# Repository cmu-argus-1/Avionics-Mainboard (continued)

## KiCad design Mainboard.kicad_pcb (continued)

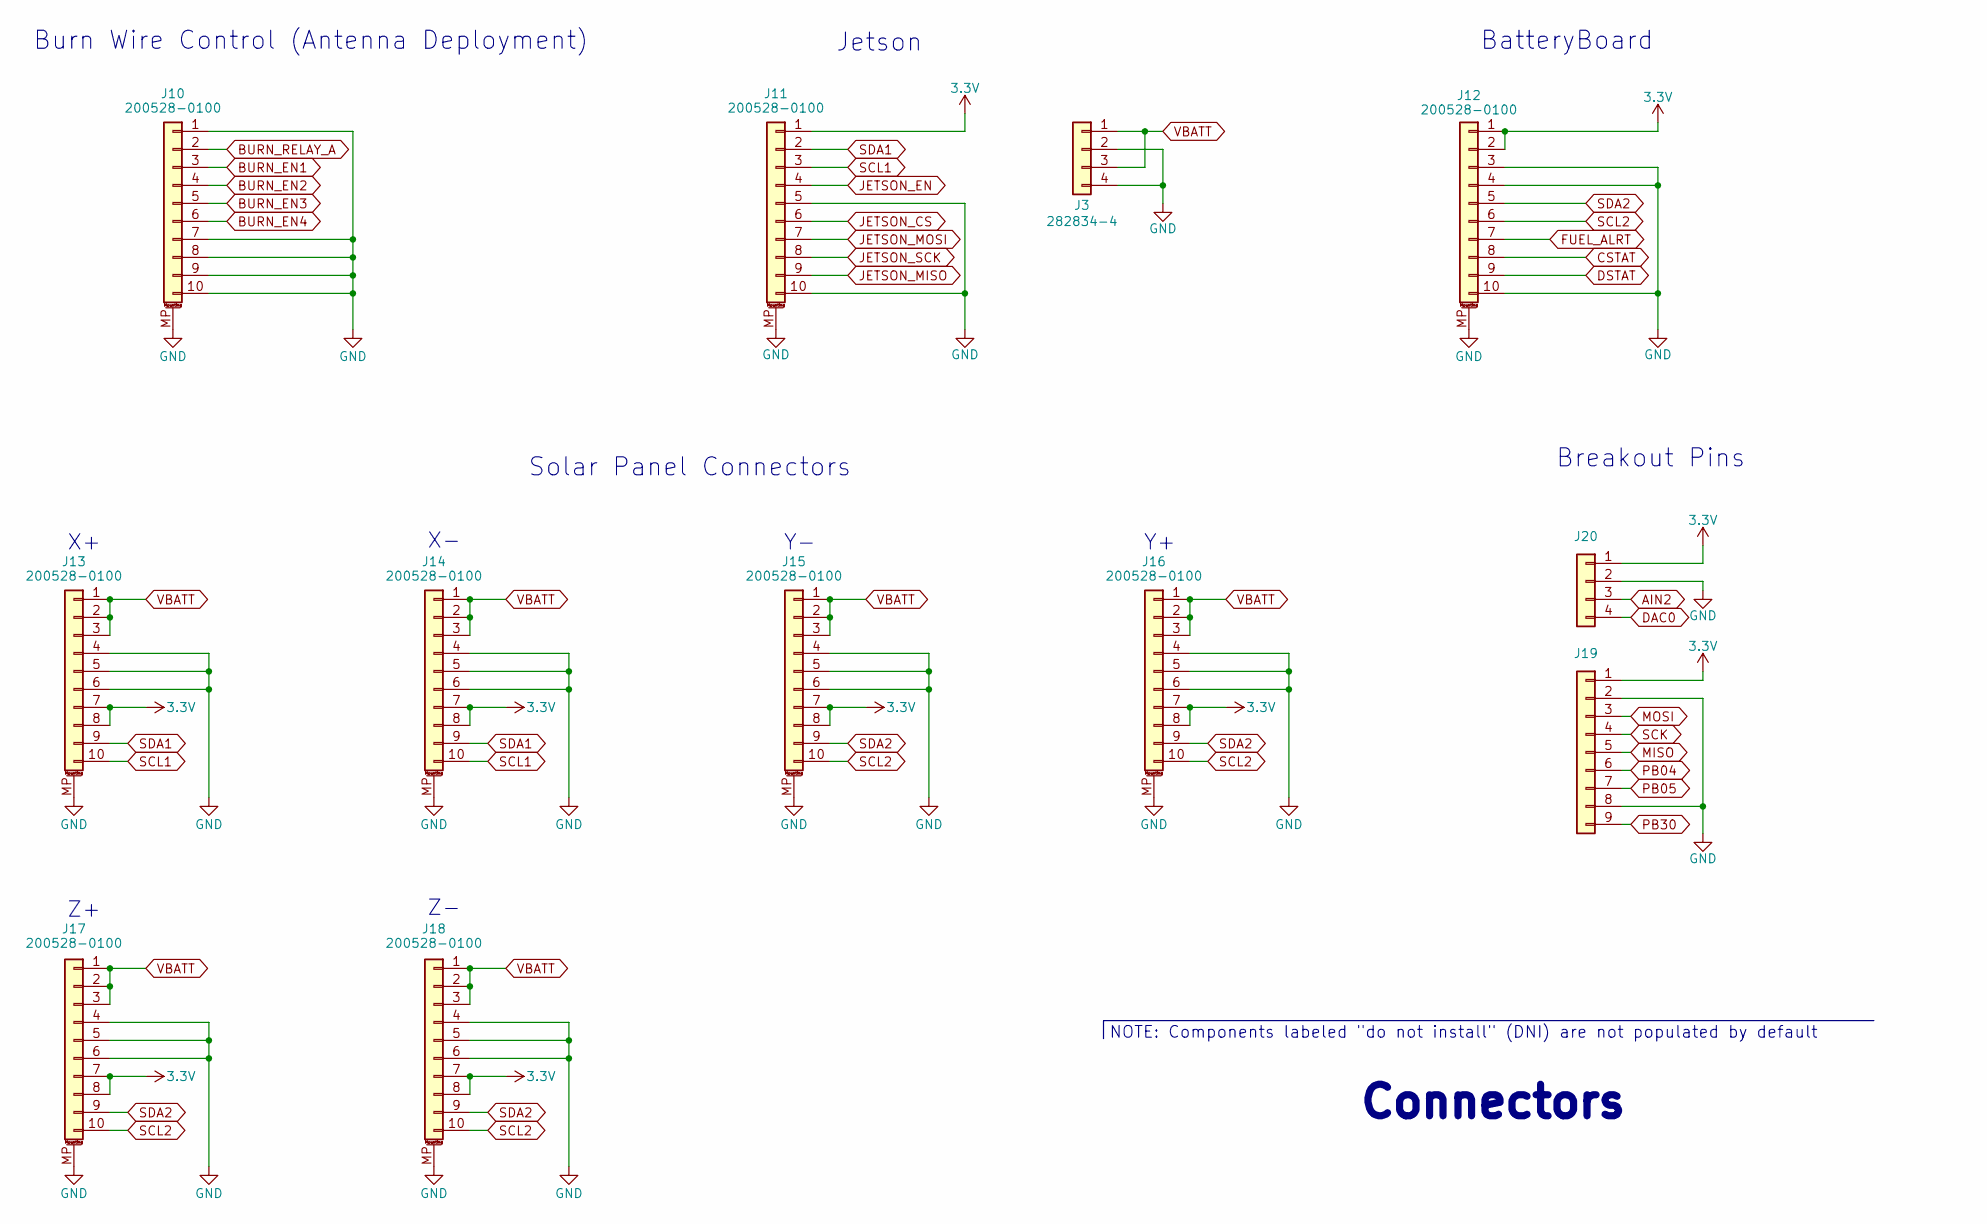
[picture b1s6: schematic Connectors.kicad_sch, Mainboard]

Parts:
J3: 282834-4; TE_282834-4
J10, J11, J12, J13, J14, J15, J16, J17, J18: 200528-0100; Molex_200528-0100_1x10-1MP_P1.00mm_Horizontal
J19: Conn_01x09; PinHeader_1x09_P2.54mm_Vertical
J20: Conn_01x04; PinHeader_1x04_P2.54mm_Vertical

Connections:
3.3V: J11.1, J12.1, J12.2, J13.7, J13.8, J14.7, J14.8, J15.7, J15.8, J16.7, J16.8, J17.7, J17.8, J18.7, J18.8, J19.1, J20.1; also elsewhere on the board
AIN2: J20.3; also elsewhere on the board
BURN_EN1: J10.3; also elsewhere on the board
BURN_EN2: J10.4; also elsewhere on the board
BURN_EN3: J10.5; also elsewhere on the board
BURN_EN4: J10.6; also elsewhere on the board
BURN_RELAY_A: J10.2; also elsewhere on the board
CSTAT: J12.8; also elsewhere on the board
DAC0: J20.4; also elsewhere on the board
DSTAT: J12.9
FUEL_ALRT: J12.7; also elsewhere on the board
GND: J3.2, J3.4, J10.1, J10.7, J10.8, J10.9, J10.10, J10.MP (MountPin), J11.5, J11.10, J11.MP (MountPin), J12.3, J12.4, J12.10, J12.MP (MountPin), J13.4, J13.5, J13.6, J13.MP (MountPin), J14.4, J14.5, J14.6, J14.MP (MountPin), J15.4, J15.5, J15.6, J15.MP (MountPin), J16.4, J16.5, J16.6, J16.MP (MountPin), J17.4, J17.5, J17.6, J17.MP (MountPin), J18.4, J18.5, J18.6, J18.MP (MountPin), J19.2, J19.8, J20.2; also elsewhere on the board
JETSON_CS: J11.6; also elsewhere on the board
JETSON_EN: J11.4; also elsewhere on the board
JETSON_MISO: J11.9; also elsewhere on the board
JETSON_MOSI: J11.7; also elsewhere on the board
JETSON_SCK: J11.8; also elsewhere on the board
MISO: J19.5; also elsewhere on the board
MOSI: J19.3; also elsewhere on the board
PB04: J19.6; also elsewhere on the board
PB05: J19.7; also elsewhere on the board
PB30: J19.9; also elsewhere on the board
SCK: J19.4; also elsewhere on the board
SCL1: J11.3, J13.10, J14.10; also elsewhere on the board
SCL2: J12.6, J15.10, J16.10, J17.10, J18.10; also elsewhere on the board
SDA1: J11.2, J13.9, J14.9; also elsewhere on the board
SDA2: J12.5, J15.9, J16.9, J17.9, J18.9; also elsewhere on the board
VBATT: J3.1, J3.3, J13.1, J13.2, J13.3, J14.1, J14.2, J14.3, J15.1, J15.2, J15.3, J16.1, J16.2, J16.3, J17.1, J17.2, J17.3, J18.1, J18.2, J18.3; also elsewhere on the board

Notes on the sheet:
BatteryBoard
Burn Wire Control (Antenna Deployment)
Connectors
NOTE: Components labeled "do not install" (DNI) are not populated by default
Solar Panel Connectors
Breakout Pins
Jetson

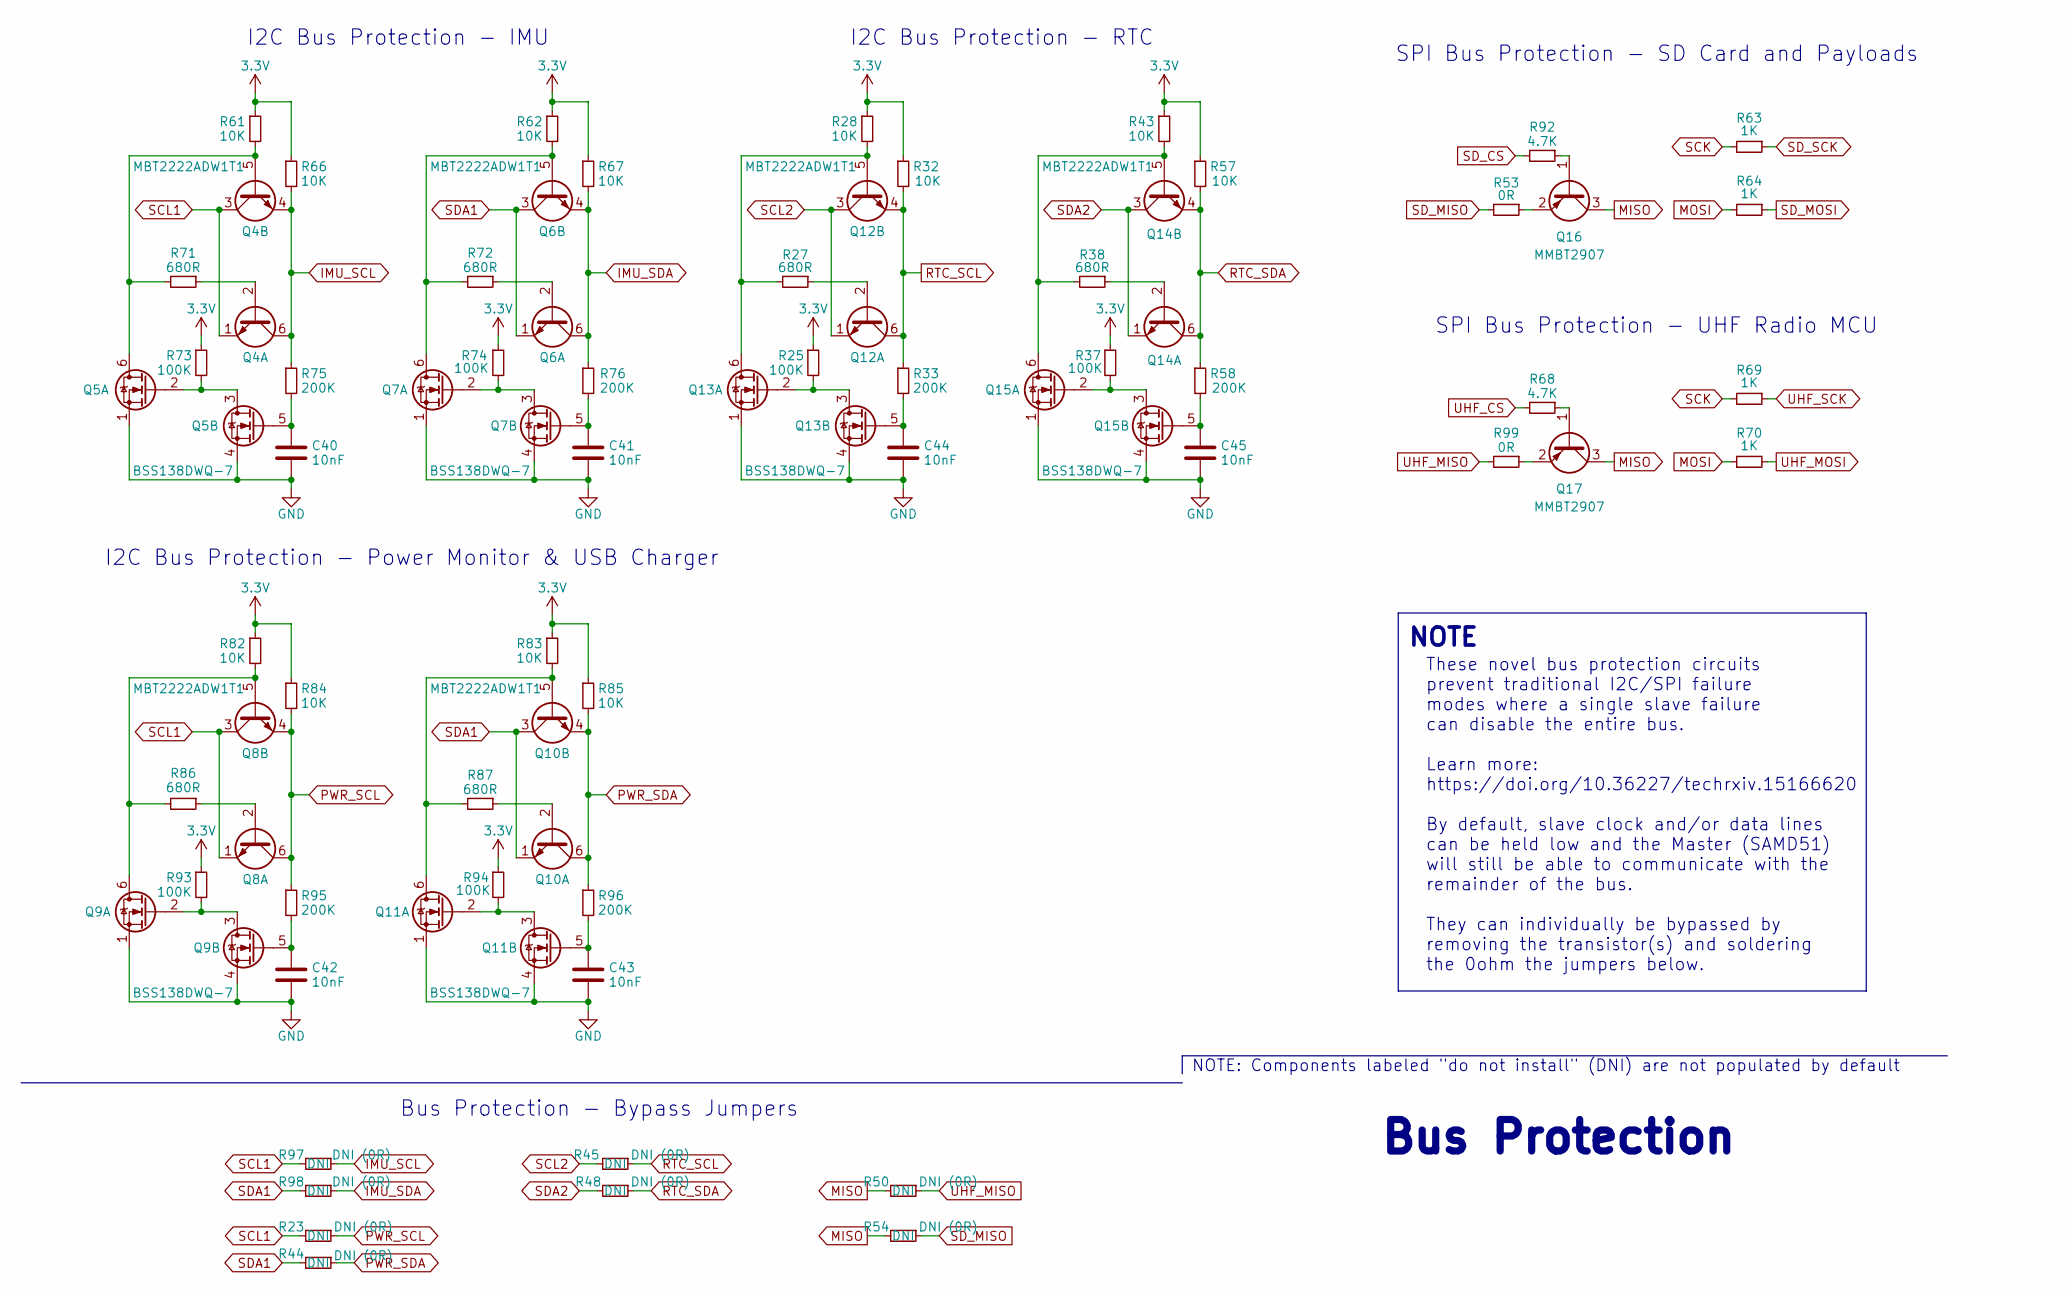
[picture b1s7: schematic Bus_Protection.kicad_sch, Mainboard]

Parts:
C40, C41, C42, C43, C44, C45: 10nF; C_0603_1608Metric
Q4, Q6, Q8, Q10, Q12, Q14: MBT2222ADW1T1; SOT-363_SC-70-6; Manufacturer_Part_Number MBT2222ADW1T1G
Q5, Q7, Q9, Q11, Q13, Q15: BSS138DWQ-7; SOT-363_SC-70-6; Manufacturer_Part_Number BSS138DWQ-7
Q16, Q17: MMBT2907; SOT-23
R23, R44, R45, R48, R50, R54, R97, R98: DNI (0R); R_0603_1608Metric
R25, R37, R73, R74, R93, R94: 100K; R_0603_1608Metric
R27, R38, R71, R72, R86, R87: 680R; R_0603_1608Metric
R28, R32, R43, R57, R61, R62, R66, R67, R82, R83, R84, R85: 10K; R_0603_1608Metric
R33, R58, R75, R76, R95, R96: 200K; R_0603_1608Metric
R53, R99: 0R; R_0603_1608Metric
R63, R64, R69, R70: 1K; R_0603_1608Metric
R68, R92: 4.7K; R_0603_1608Metric

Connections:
3.3V: R25.1, R28.1, R32.1, R37.1, R43.1, R57.1, R61.1, R62.1, R66.1, R67.1, R73.1, R74.1, R82.1, R83.1, R84.1, R85.1, R93.1, R94.1; also elsewhere on the board
GND: C40.2, C41.2, C42.2, C43.2, C44.2, C45.2, Q5.1 (S2), Q5.4 (S1), Q7.1 (S2), Q7.4 (S1), Q9.1 (S2), Q9.4 (S1), Q11.1 (S2), Q11.4 (S1), Q13.1 (S2), Q13.4 (S1), Q15.1 (S2), Q15.4 (S1); also elsewhere on the board
IMU_SCL: Q4.4 (E2), Q4.6 (C1), R66.2, R75.1, R97.1; also elsewhere on the board
IMU_SDA: Q6.4 (E2), Q6.6 (C1), R67.2, R76.1, R98.1; also elsewhere on the board
MISO: Q16.3 (C), Q17.3 (C), R50.2, R54.2; also elsewhere on the board
MOSI: R64.2, R70.1; also elsewhere on the board
unnamed: Q4.2 (B1), R71.1
unnamed: Q4.5 (B2), Q5.6 (D1), R61.2, R71.2
unnamed: Q5.2 (G2), Q5.3 (D2), R73.2
unnamed: C40.1, Q5.5 (G1), R75.2
unnamed: Q6.2 (B1), R72.1
unnamed: Q6.5 (B2), Q7.6 (D1), R62.2, R72.2
unnamed: Q7.2 (G2), Q7.3 (D2), R74.2
unnamed: C41.1, Q7.5 (G1), R76.2
unnamed: Q8.2 (B1), R86.1
unnamed: Q8.5 (B2), Q9.6 (D1), R82.2, R86.2
unnamed: Q9.2 (G2), Q9.3 (D2), R93.2
unnamed: C42.1, Q9.5 (G1), R95.2
unnamed: Q10.2 (B1), R87.1
unnamed: Q10.5 (B2), Q11.6 (D1), R83.2, R87.2
unnamed: Q11.2 (G2), Q11.3 (D2), R94.2
unnamed: C43.1, Q11.5 (G1), R96.2
unnamed: Q12.2 (B1), R27.1
unnamed: Q12.5 (B2), Q13.6 (D1), R27.2, R28.2
unnamed: Q13.2 (G2), Q13.3 (D2), R25.2
unnamed: C44.1, Q13.5 (G1), R33.2
unnamed: Q14.2 (B1), R38.1
unnamed: Q14.5 (B2), Q15.6 (D1), R38.2, R43.2
unnamed: Q15.2 (G2), Q15.3 (D2), R37.2
unnamed: C45.1, Q15.5 (G1), R58.2
unnamed: Q16.1 (B), R92.1
unnamed: Q16.2 (E), R53.1
unnamed: Q17.1 (B), R68.1
unnamed: Q17.2 (E), R99.1
PWR_SCL: Q8.4 (E2), Q8.6 (C1), R23.1, R84.2, R95.1; also elsewhere on the board
PWR_SDA: Q10.4 (E2), Q10.6 (C1), R44.1, R85.2, R96.1; also elsewhere on the board
RTC_SCL: Q12.4 (E2), Q12.6 (C1), R32.2, R33.1, R45.1; also elsewhere on the board
RTC_SDA: Q14.4 (E2), Q14.6 (C1), R48.1, R57.2, R58.1; also elsewhere on the board
SCK: R63.2, R69.2; also elsewhere on the board
SCL1: Q4.1 (E1), Q4.3 (C2), Q8.1 (E1), Q8.3 (C2), R23.2, R97.2; also elsewhere on the board
SCL2: Q12.1 (E1), Q12.3 (C2), R45.2; also elsewhere on the board
SDA1: Q6.1 (E1), Q6.3 (C2), Q10.1 (E1), Q10.3 (C2), R44.2, R98.2; also elsewhere on the board
SDA2: Q14.1 (E1), Q14.3 (C2), R48.2; also elsewhere on the board
SD_CS: R92.2; also elsewhere on the board
SD_MISO: R53.2, R54.1; also elsewhere on the board
SD_MOSI: R64.1; also elsewhere on the board
SD_SCK: R63.1; also elsewhere on the board
UHF_CS: R68.2; also elsewhere on the board
UHF_MISO: R50.1, R99.2; also elsewhere on the board
UHF_MOSI: R70.2; also elsewhere on the board
UHF_SCK: R69.1; also elsewhere on the board

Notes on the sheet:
I2C Bus Protection - RTC
I2C Bus Protection - Power Monitor & USB Charger
SPI Bus Protection - UHF Radio MCU
SPI Bus Protection - SD Card and Payloads
These novel bus protection circuits prevent traditional I2C/SPI failure modes where a single slave failure can disable the entire bus. Learn more: https://doi.org/10.36227/techrxiv.15166620 By default, slave clock and/or data lines can be held low and the Master (SAMD51) will still be able to commu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
NOTE
I2C Bus Protection - IMU
Bus Protection - Bypass Jumpers
NOTE: Components labeled "do not install" (DNI) are not populated by default
Bus Protection

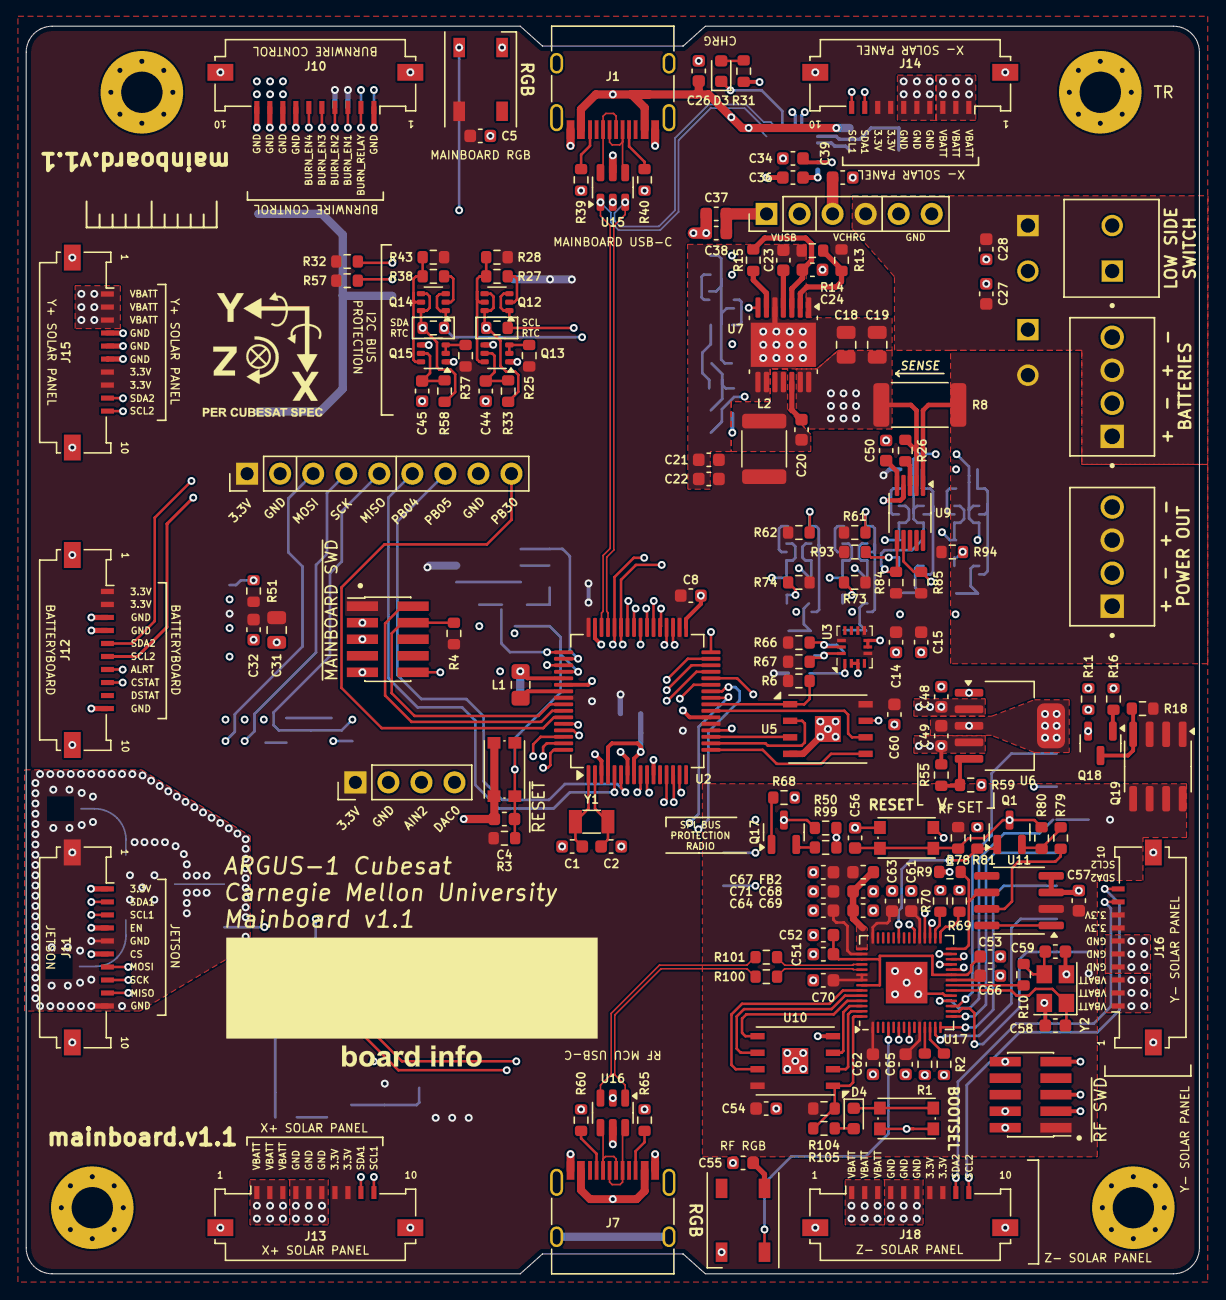
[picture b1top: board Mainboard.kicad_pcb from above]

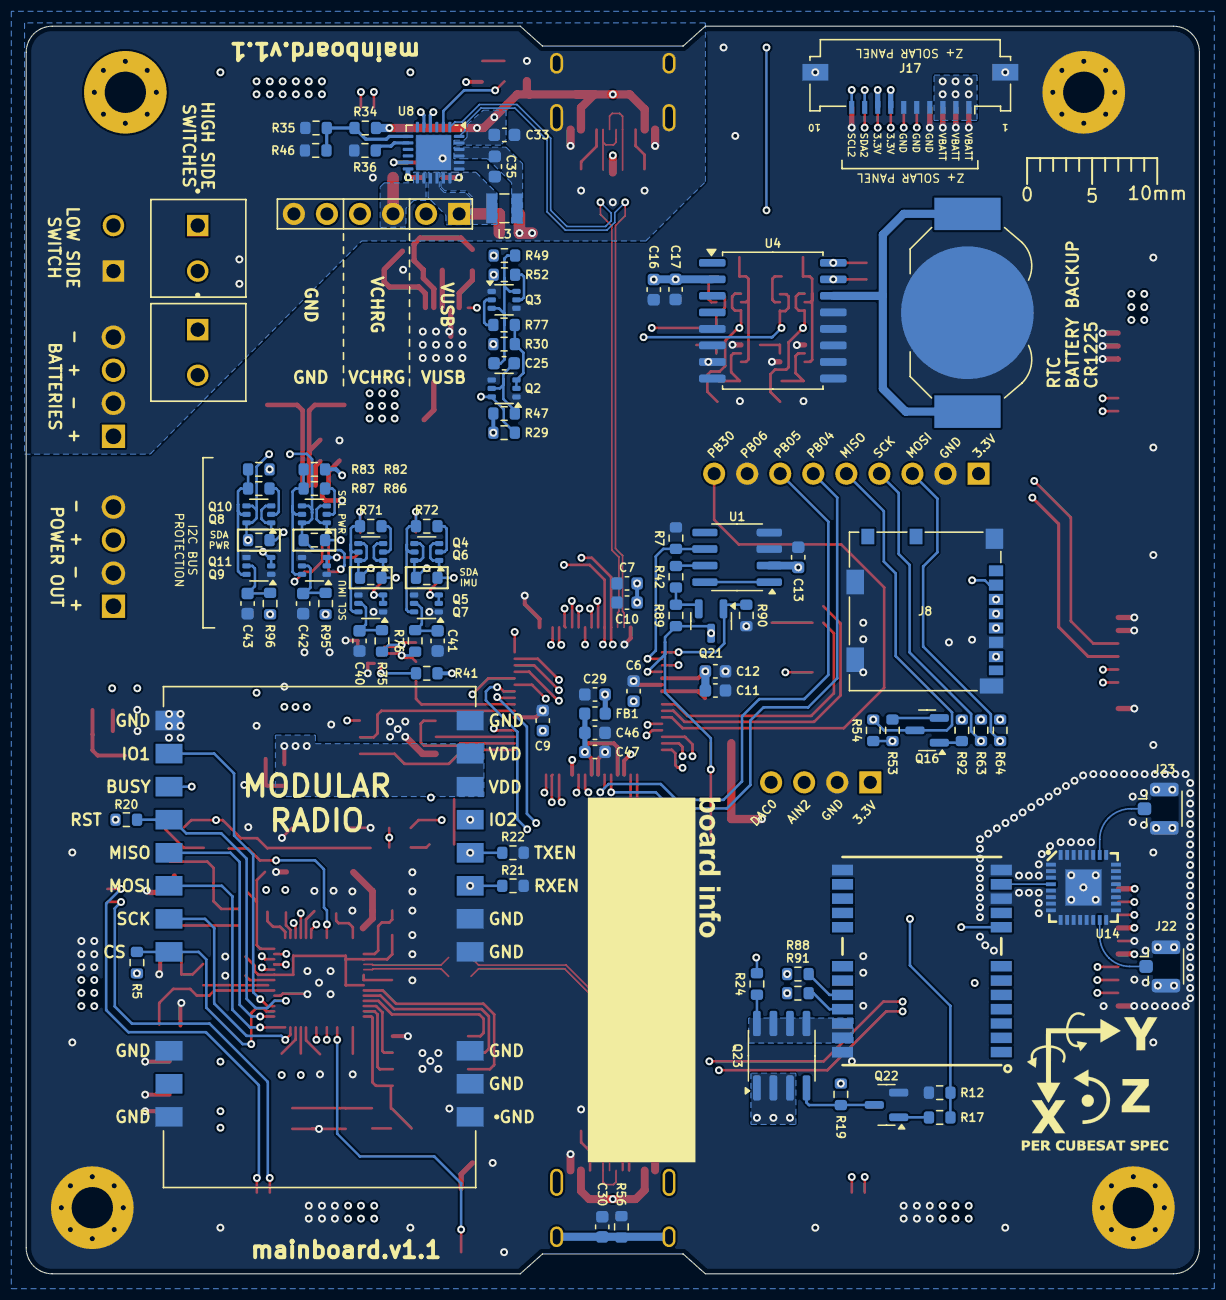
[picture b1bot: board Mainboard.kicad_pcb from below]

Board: 4 copper layers, 90.2 x 95.9 mm, 255 parts (94 on the bottom side), 191 nets.

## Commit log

2024-06-18 Upload .gitignore
2024-06-22 Upload Files
2024-06-28 Complete layout
2024-07-02 Updated Mounting Holes
2024-07-19 v1 Final
2024-09-10 Fixed/Added I2C addresses to schematic
2024-09-23 v1.1 Schematic
2024-09-24 v1.1 Layout
2024-11-19 Stash
